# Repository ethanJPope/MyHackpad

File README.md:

# BOM

-16 Gateron Milky Yellows switches

-16 Through Hole 1N4148 Diodes

-16 Keycaps

-1 EC11 Rotary encoder

-1 PCB

-1 Through Hole Seeed XIAO RP2040

-1 Case

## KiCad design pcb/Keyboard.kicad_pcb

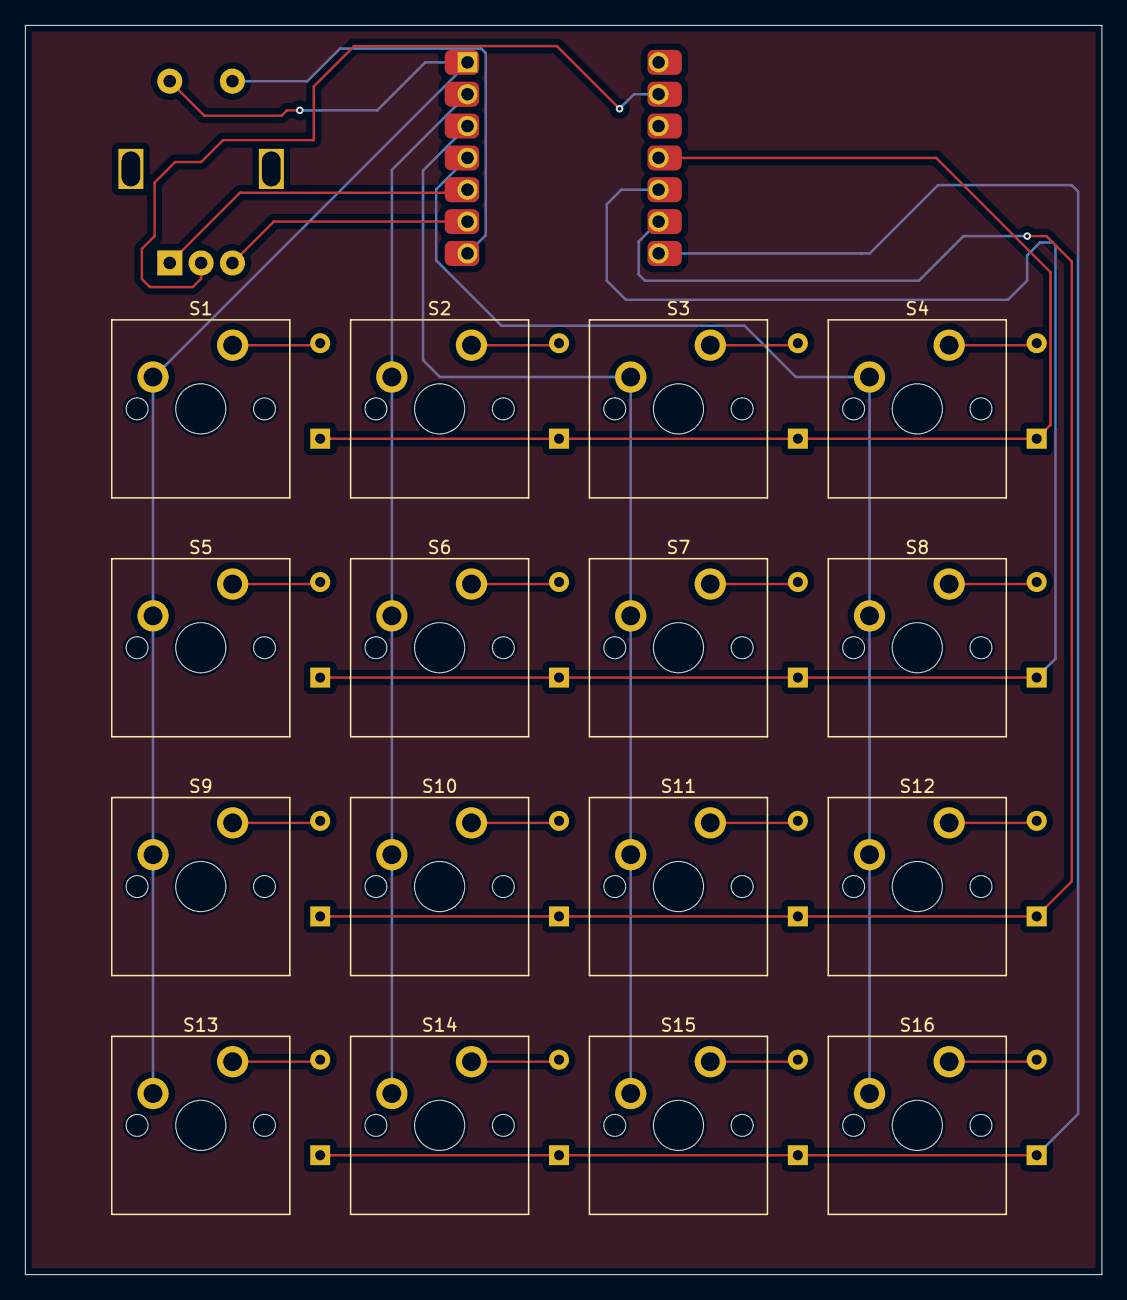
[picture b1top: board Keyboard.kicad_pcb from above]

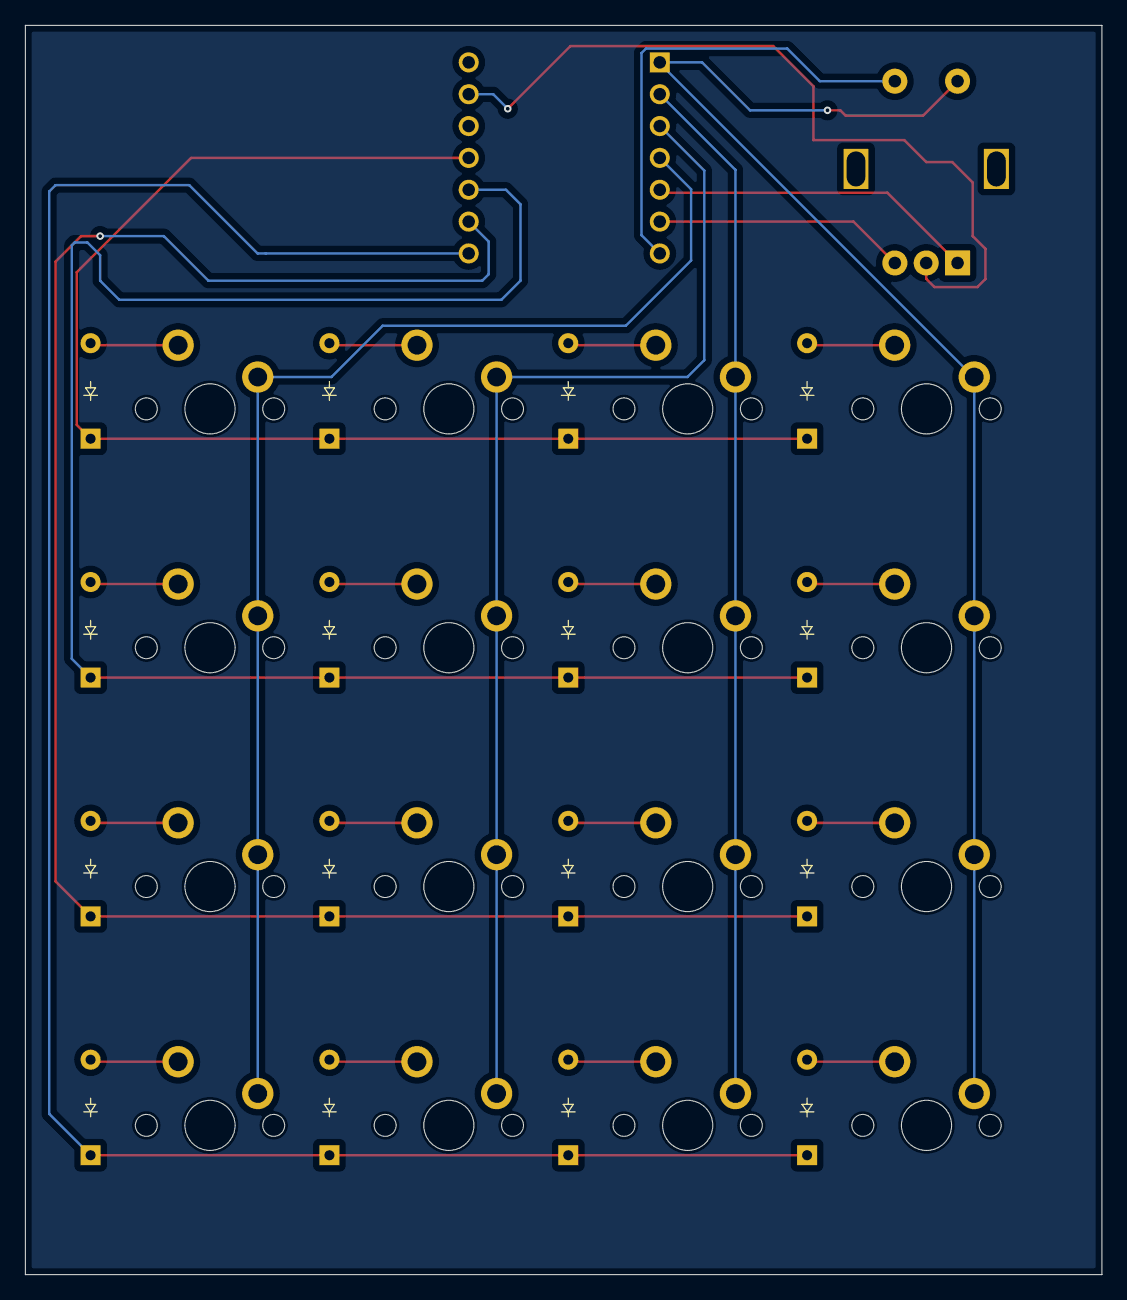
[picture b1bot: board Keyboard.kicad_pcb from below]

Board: 2 copper layers, 85.9 x 99.6 mm, 34 parts (16 on the bottom side), 28 nets.

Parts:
D1, D2, D3, D4, D5, D6, D7, D8, D9, D10, D11, D12, D13, D14, D15, D16: Diode; Diode_DO-35
S1, S2, S3, S4, S5, S6, S7, S8, S9, S10, S11, S12, S13, S14, S15, S16: Keyswitch; MX_PCB_1.00u
SW2: RotaryEncoder_Switch; Encoder_EC11_MX
U1: MCU_Seeed_XIAO_RP2040; Seeed_XIAO_RP2040

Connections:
Collum 1: S1.1, S5.1, S9.1, S13.1, SW2.S2, U1.1 (PA02_A0_D0)
Collum 2: S2.1, S6.1, S10.1, S14.1, U1.2 (PA4_A1_D1)
Collum 3: S3.1, S7.1, S11.1, S15.1, U1.3 (PA10_A2_D2)
Collum 4: S4.1, S8.1, S12.1, S16.1, U1.4 (PA11_A3_D3)
GND: SW2.C, U1.13 (GND)
unnamed: D1.2 (A), S1.2
unnamed: D2.2 (A), S2.2
unnamed: D3.2 (A), S3.2
unnamed: D4.2 (A), S4.2
unnamed: D5.2 (A), S5.2
unnamed: D6.2 (A), S6.2
unnamed: D7.2 (A), S7.2
unnamed: D8.2 (A), S8.2
unnamed: D9.2 (A), S9.2
unnamed: D10.2 (A), S10.2
unnamed: D11.2 (A), S11.2
unnamed: D12.2 (A), S12.2
unnamed: D13.2 (A), S13.2
unnamed: D14.2 (A), S14.2
unnamed: D15.2 (A), S15.2
unnamed: D16.2 (A), S16.2
unnamed: SW2.A, U1.5 (PA8_A4_D4_SDA)
unnamed: SW2.B, U1.6 (PA9_A5_D5_SCL)
unnamed: SW2.S1, U1.7 (PB08_A6_D6_TX)
Row 0: D1.1 (K), D2.1 (K), D3.1 (K), D4.1 (K), U1.11 (PA6_A10_D10_MOSI)
Row 1: D5.1 (K), D6.1 (K), D7.1 (K), D8.1 (K), U1.10 (PA5_A9_D9_MISO)
Row 2: D9.1 (K), D10.1 (K), D11.1 (K), D12.1 (K), U1.9 (PA7_A8_D8_SCK)
Row 3: D13.1 (K), D14.1 (K), D15.1 (K), D16.1 (K), U1.8 (PB09_A7_D7_RX)

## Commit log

2024-10-13 import files
2024-10-13 making some changes
